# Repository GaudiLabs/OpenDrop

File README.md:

## OpenDrop 

Open Source Digital Microfluidics Bio Lab

### Don't click on the files!
Click on the "Download ZIP" Button to the right.
Then unpack the archive.

### Open Source Digital Microfluidics Bio Lab

OpenDrop is a new open source digital microfludics platform for research purposes. The device uses recent electro-wetting technology to control small droplets of liquids. Potential applications include lab-on-a-chip devices for automating processes of digital biology. However, the present design should also open up the technology to other fields, such as art, music, games, and education. It should also allow experimentation for the purpose of finding new applications. 

For more info on the open source project see:

http://www.gaudi.ch/OpenDrop

### License

OpenDrop, all design files and software are licensed under a GNU GENERAL PUBLIC LICENSE
See license file in the repository.

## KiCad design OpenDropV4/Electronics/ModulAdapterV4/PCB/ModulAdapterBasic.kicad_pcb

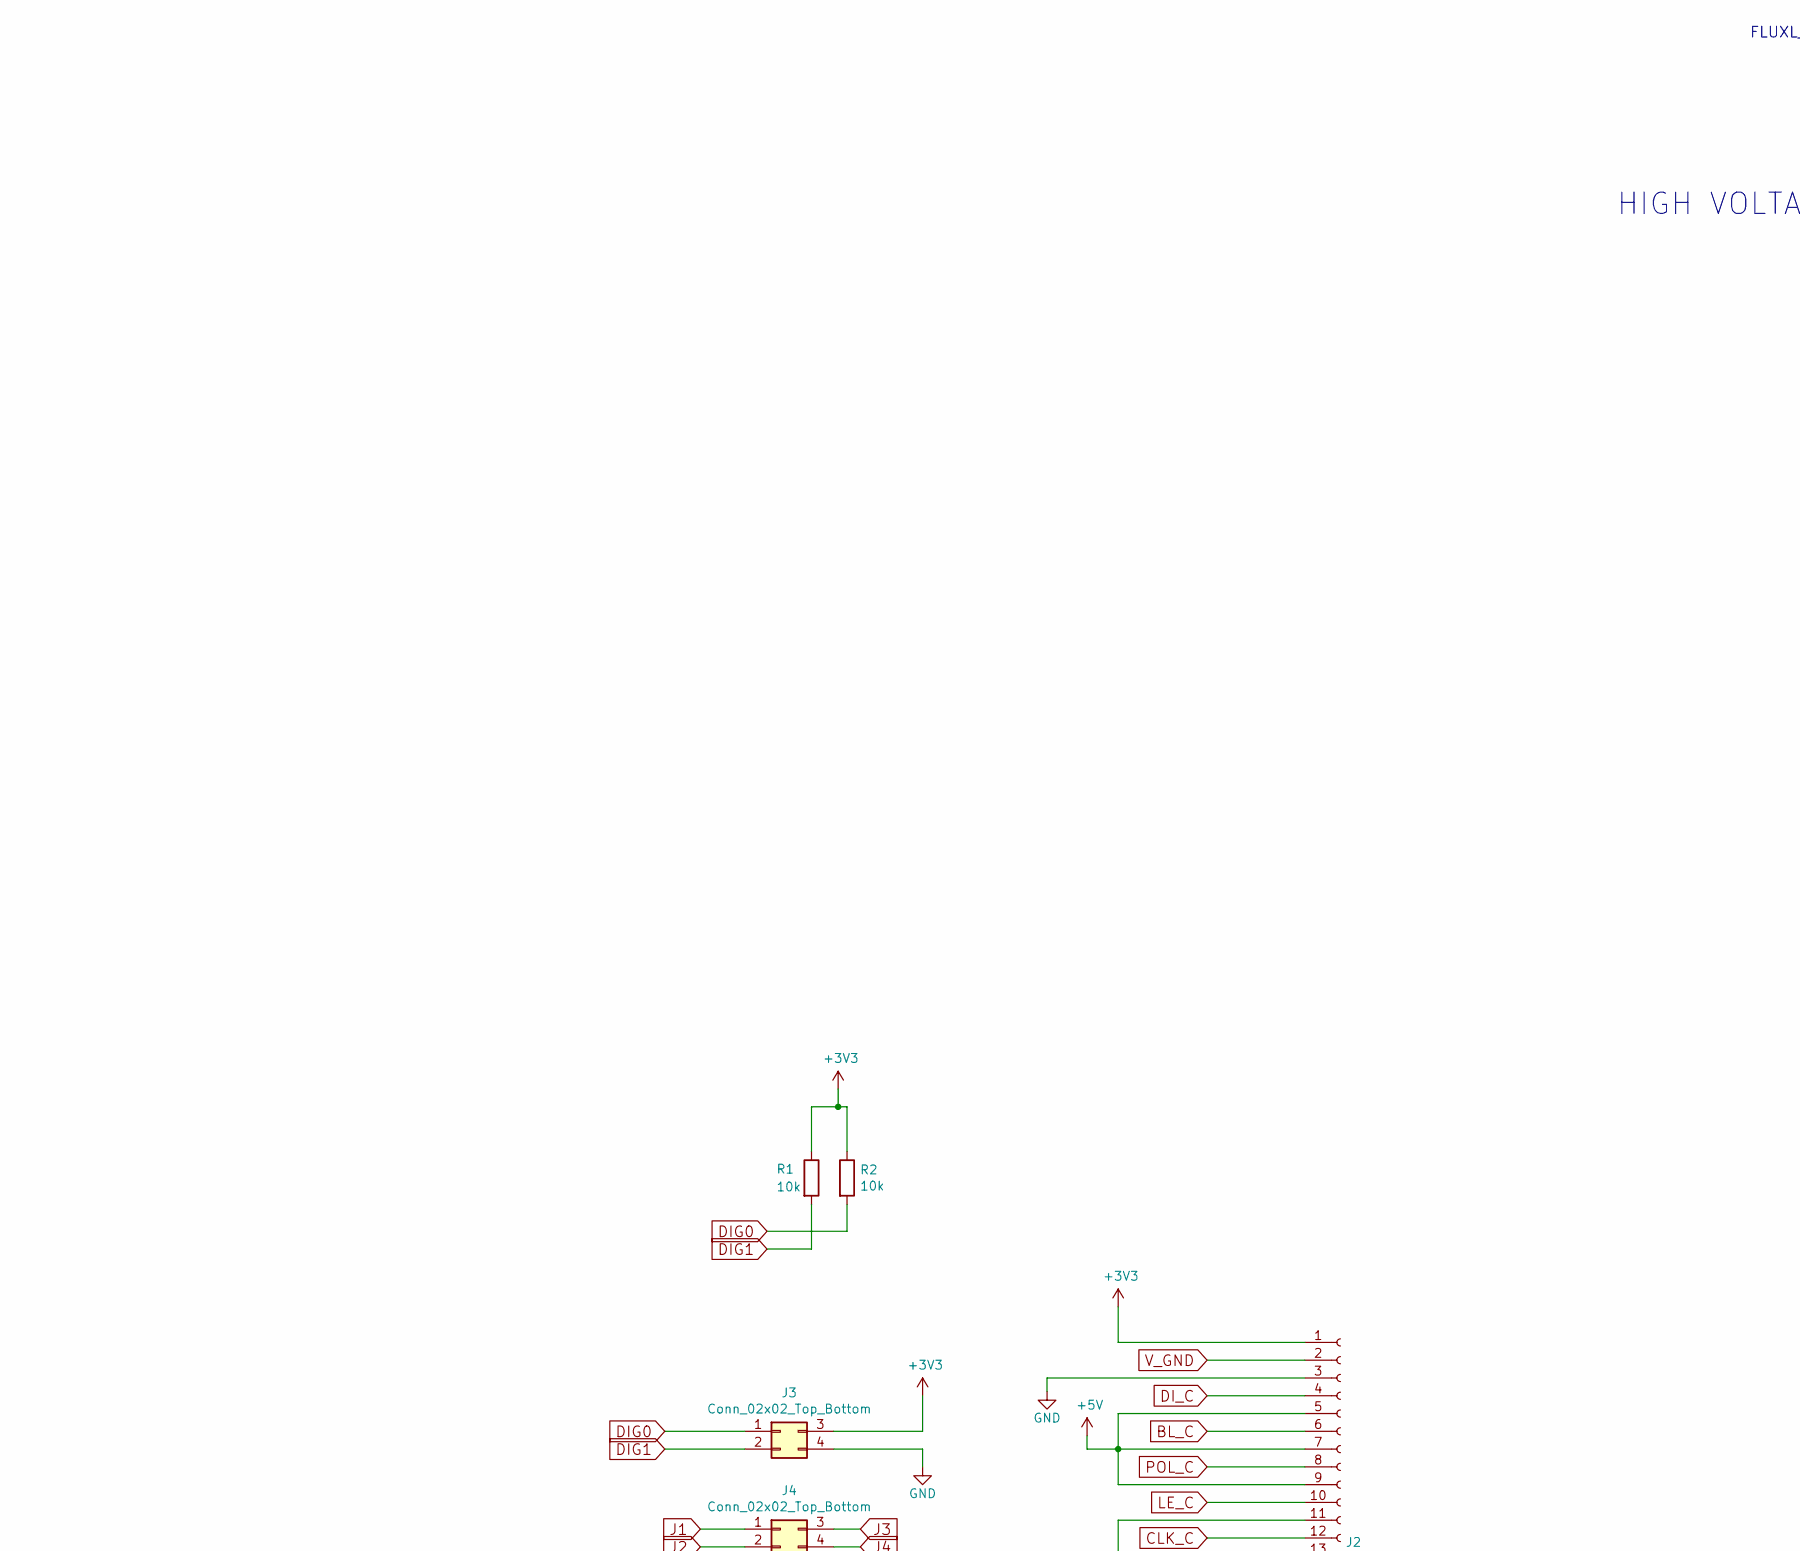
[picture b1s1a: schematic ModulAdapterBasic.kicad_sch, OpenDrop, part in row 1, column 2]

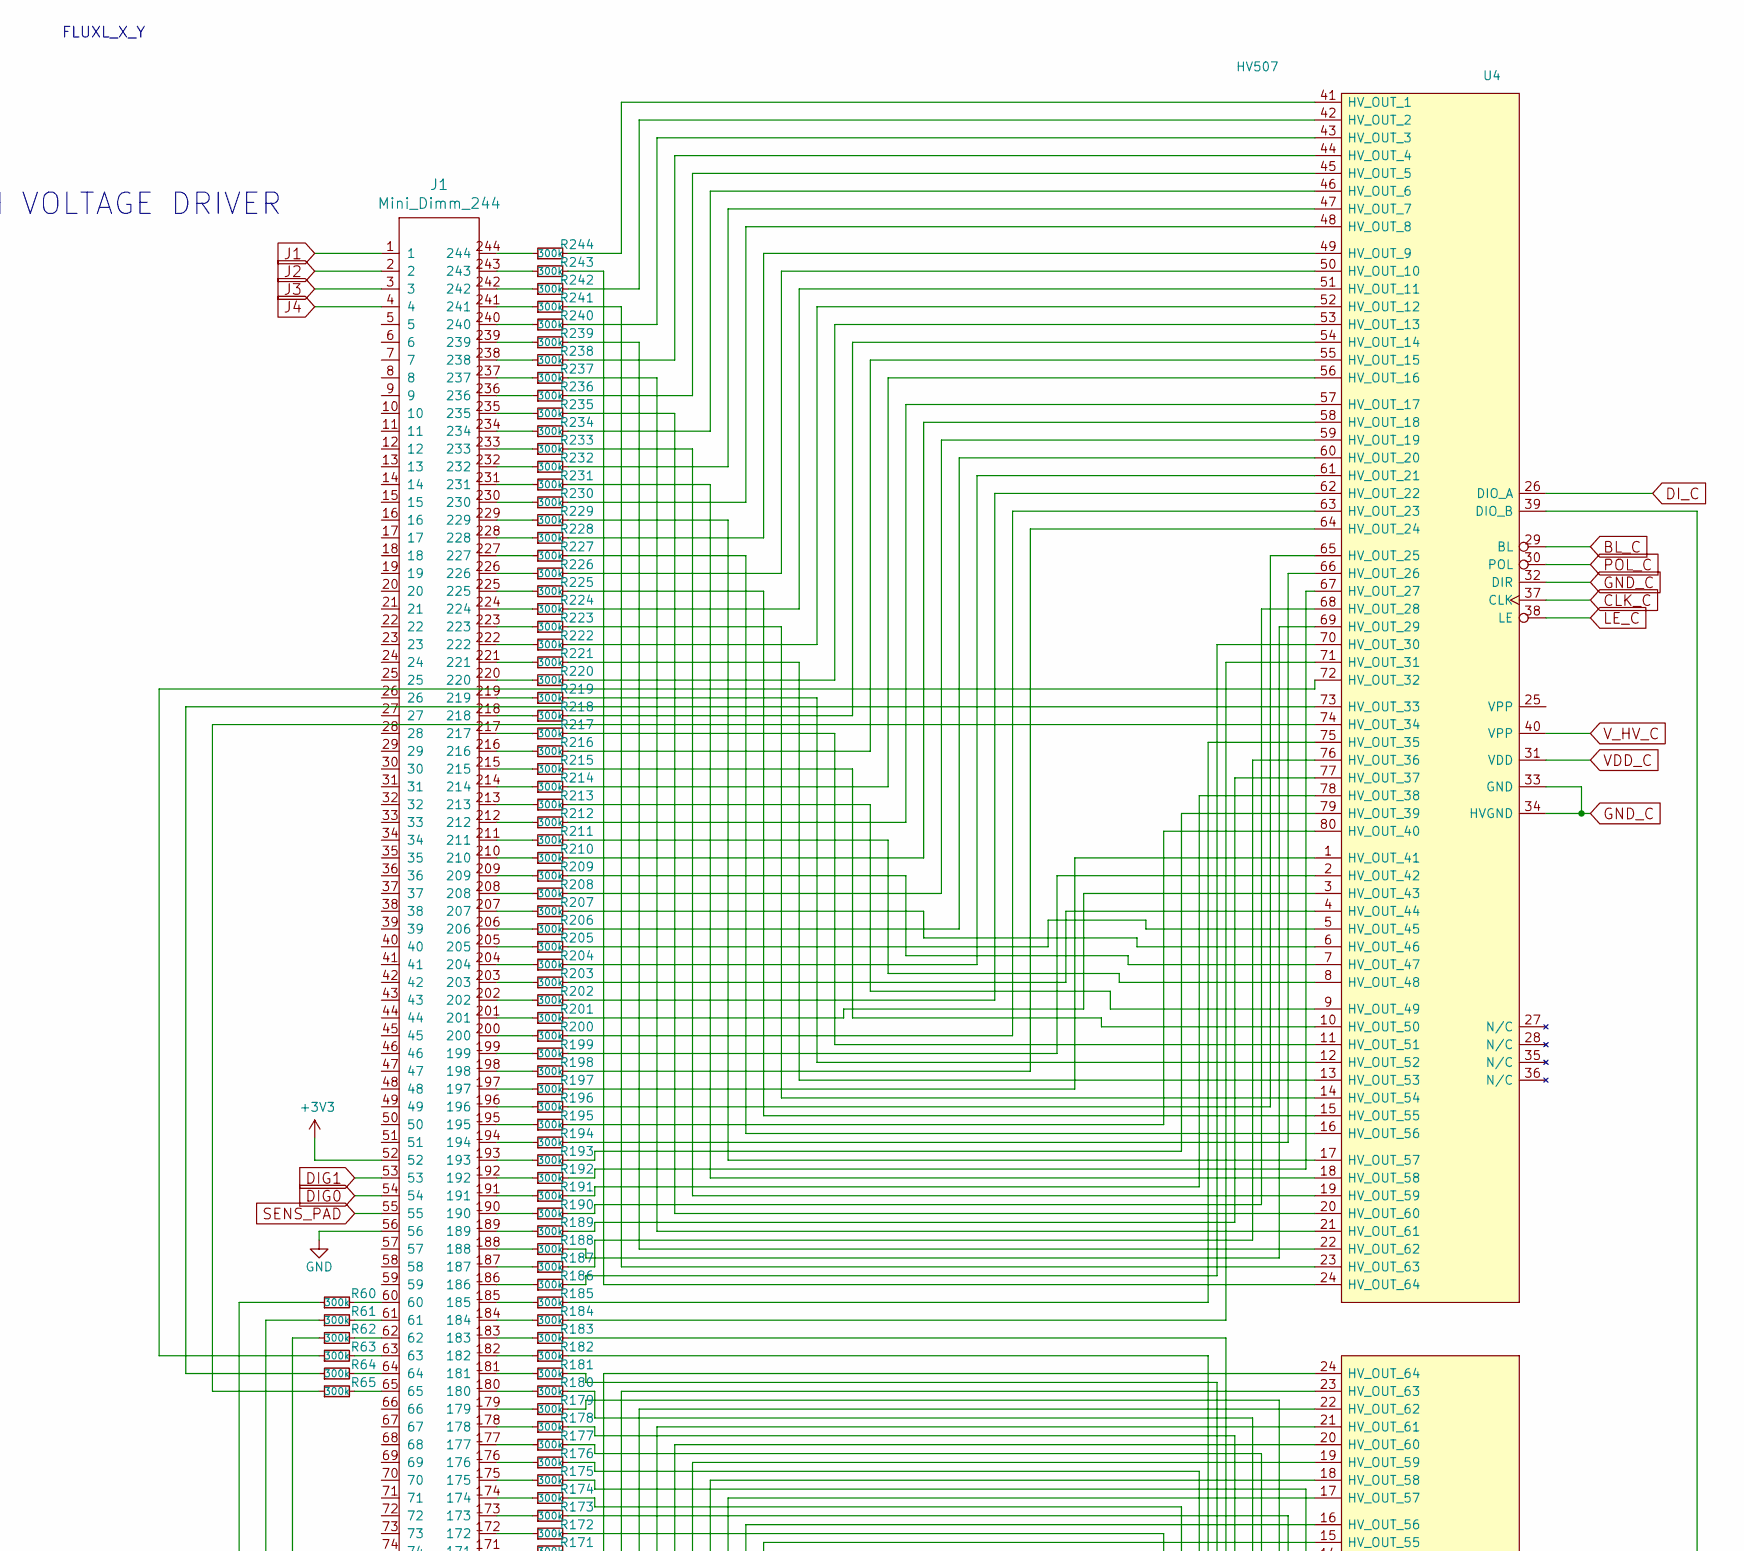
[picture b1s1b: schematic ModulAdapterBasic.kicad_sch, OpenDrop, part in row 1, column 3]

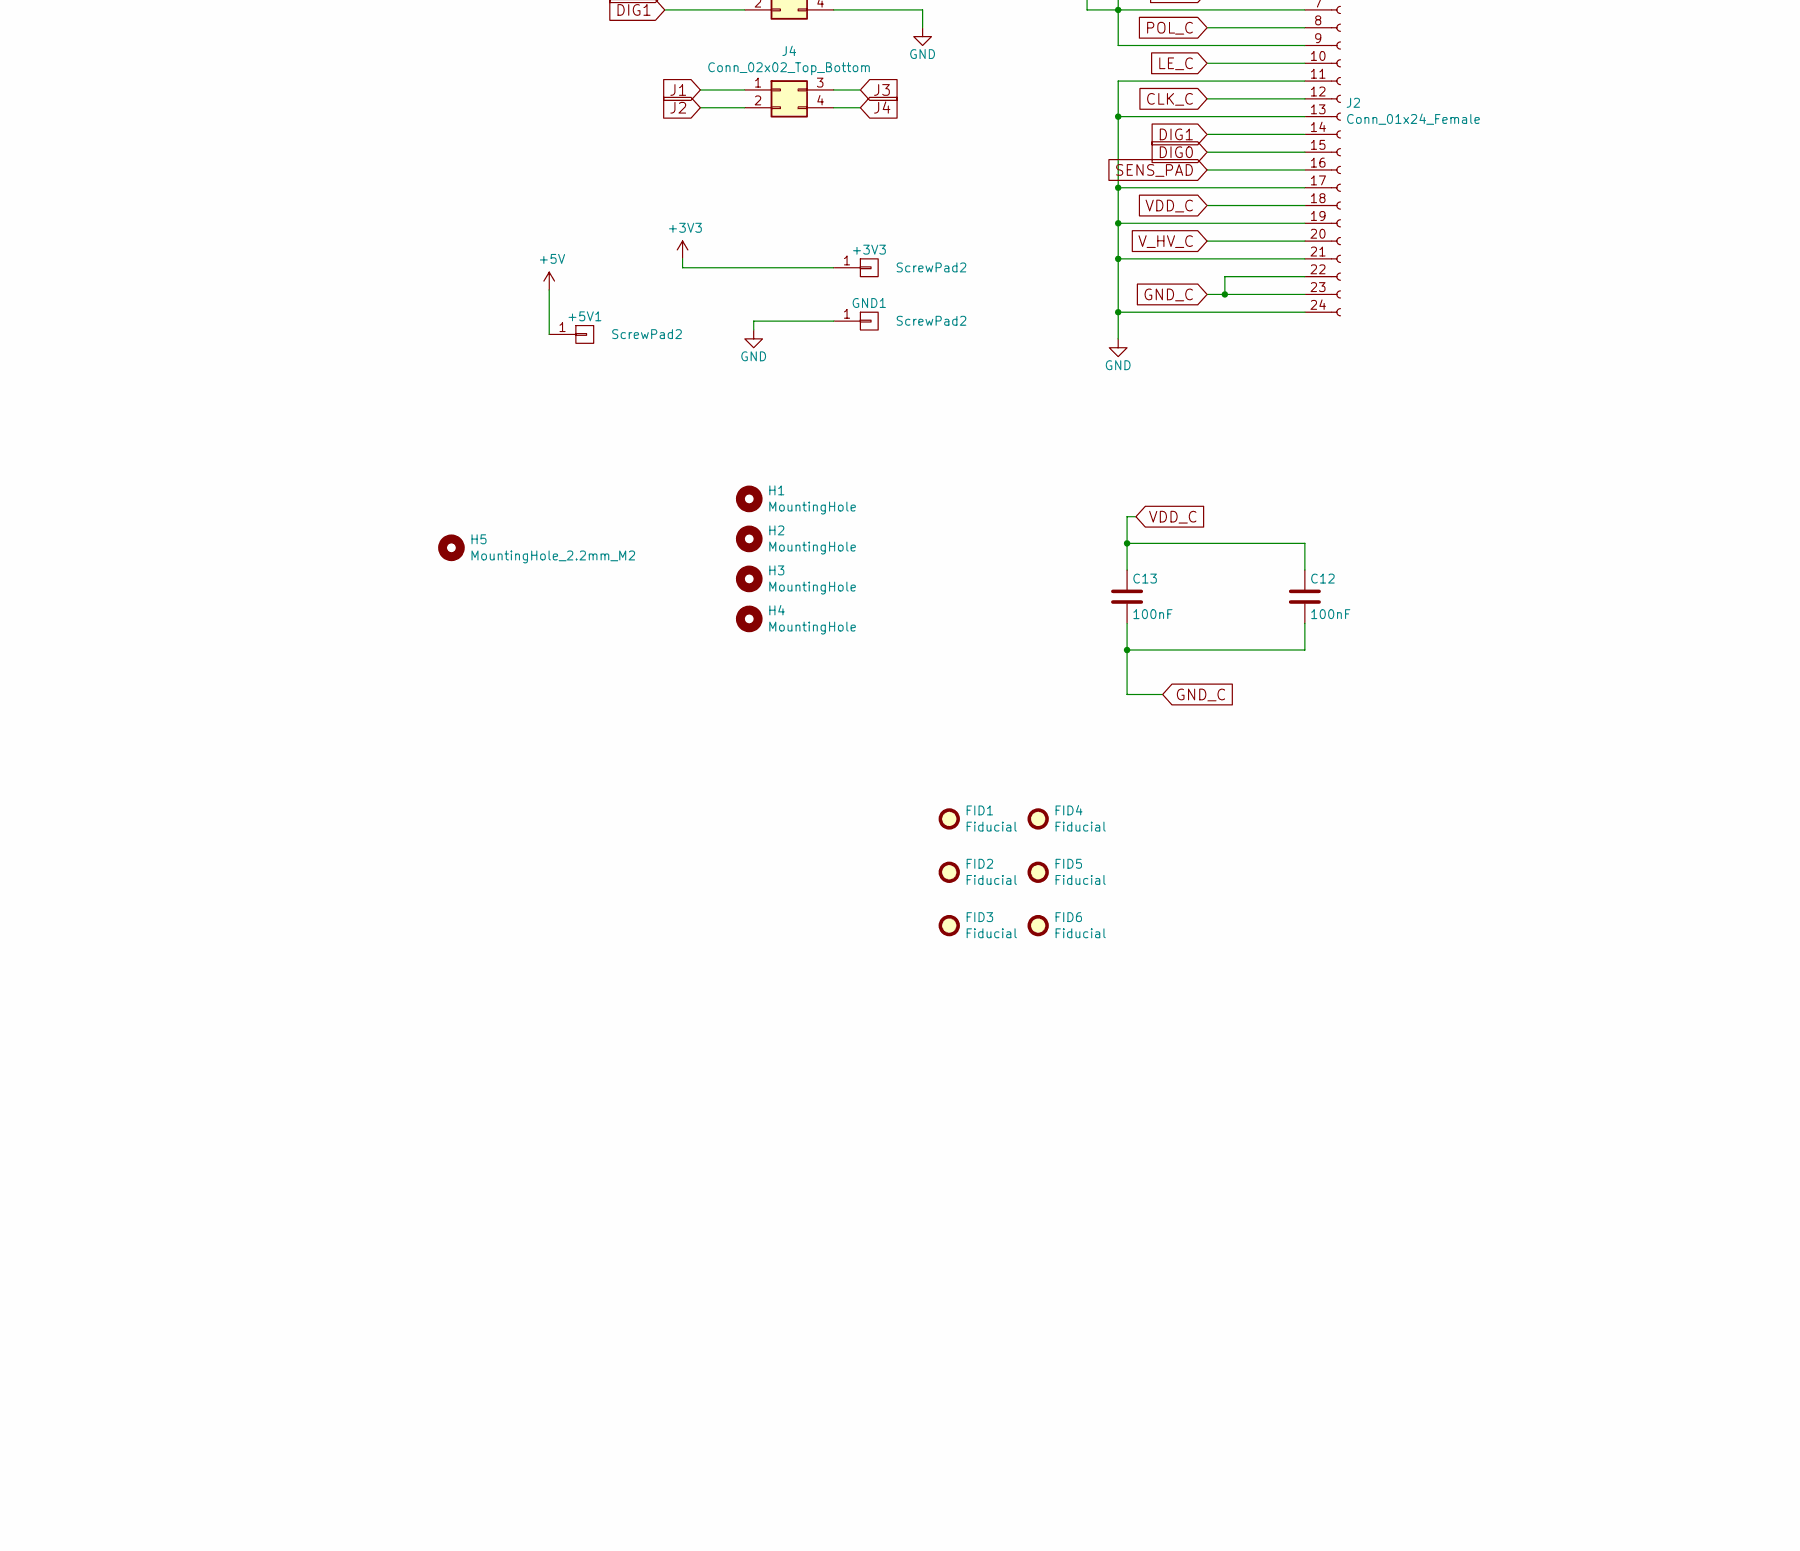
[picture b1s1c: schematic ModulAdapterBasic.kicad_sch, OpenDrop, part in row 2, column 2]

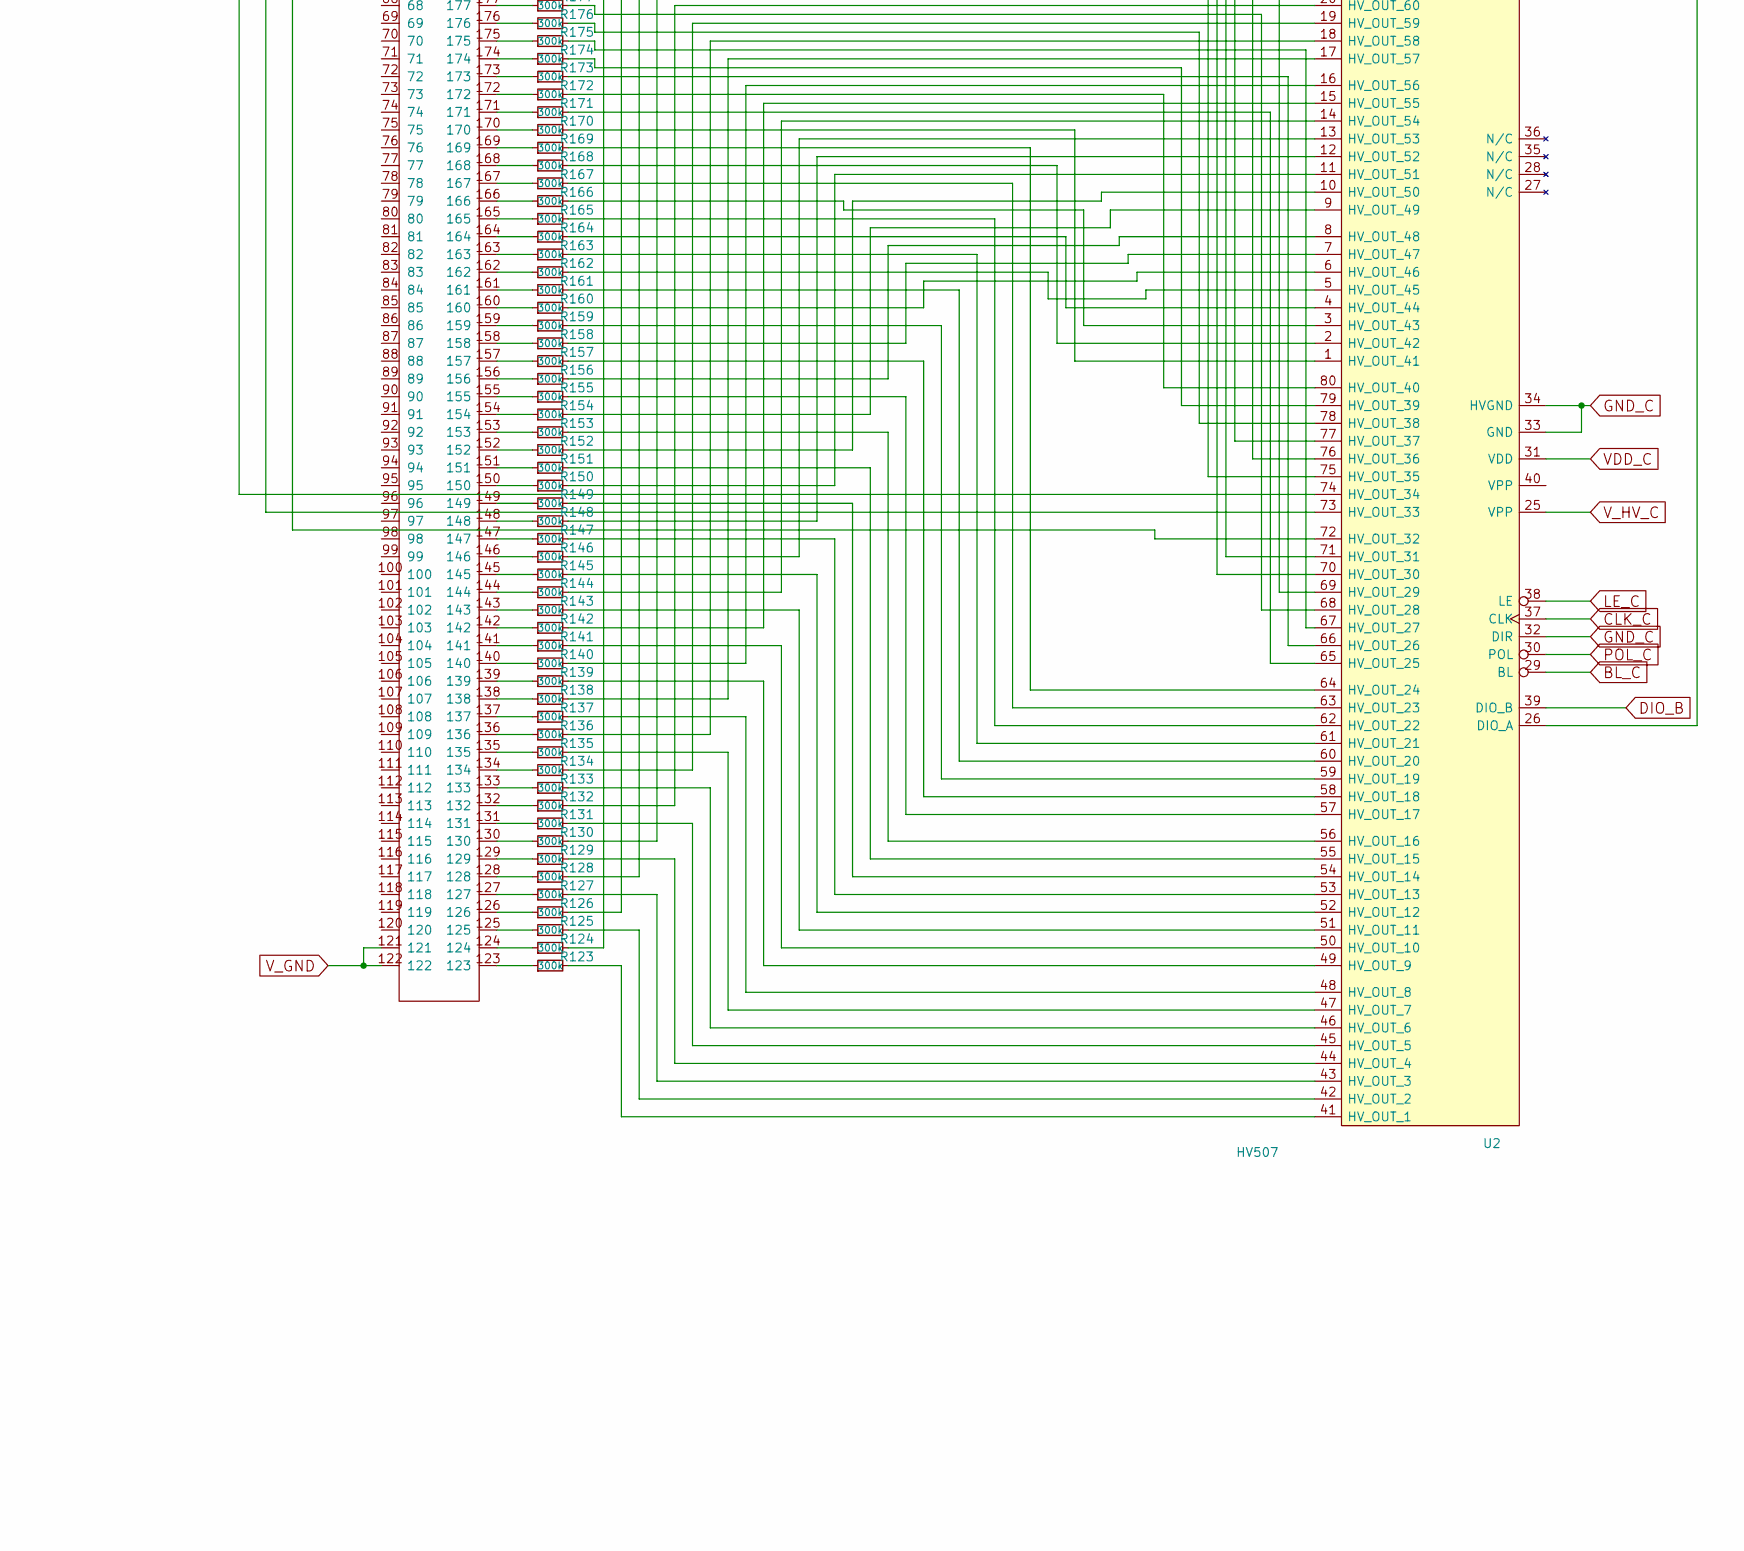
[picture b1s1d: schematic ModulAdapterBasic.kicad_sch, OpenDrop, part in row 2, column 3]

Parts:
+3V3, +5V1: ScrewPad2; Measurement_Point_Square-SMD-Pad_Small
C12, C13: 100nF; C_0603_1608Metric
FID1, FID2, FID3, FID4, FID5, FID6: Fiducial; Fiducial_1mm_Dia_2.54mm_Outer_CopperBottom
GND1: ScrewPad2; Measurement_Point_Square-SMD-Pad_Small
H1, H2, H3, H4: MountingHole; MountingHoleM3
H5: MountingHole_2.2mm_M2
J1: Mini_Dimm_244; MiniDimm_06_244_200
J2: Conn_01x24_Female; FFC_MOLEX_EASYON_05mm_24
J3, J4: Conn_02x02_Top_Bottom; PinHeader_2x02_P2.00mm_Vertical
R1, R2: 10k; R_0603_1608Metric
R60, R61, R62, R63, R64, R65, R123, R124, R125, R126, R127, R128, R129, R130, R131, R132, R133, R134, R135, R136, R137, R138, R139, R140, R141, R142, R143, R144, R145, R146, R147, R148, R149, R150, R151, R152, R153, R154, R155, R156, R157, R158, R159, R160, R161, R162, R163, R164, R165, R166, R167, R168, R169, R170, R171, R172, R173, R174, R175, R176, R177, R178, R179, R180, R181, R182, R183, R184, R185, R186, R187, R188, R189, R190, R191, R192, R193, R194, R195, R196, R197, R198, R199, R200, R201, R202, R203, R204, R205, R206, R207, R208, R209, R210, R211, R212, R213, R214, R215, R216, R217, R218, R219, R220, R221, R222, R223, R224, R225, R226, R227, R228, R229, R230, R231, R232, R233, R234, R235, R236, R237, R238, R239, R240, R241, R242, R243, R244: 300k; R_0402_1005Metric
U2, U4: HV507; PQFP-80_14x20mm_Pitch0.8mm

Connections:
+3V3: +3V3.1, J1.52, J2.1, J3.3, R1.1, R2.1
+5V: +5V1.1, J2.5, J2.7, J2.9
BL_C: J2.6, U2.29 (BL), U4.29 (BL)
CLK_C: J2.12, U2.37 (CLK), U4.37 (CLK)
DIG0: J1.54, J2.15, J3.1, R2.2
DIG1: J1.53, J2.14, J3.2, R1.2
DIO_B: U2.39 (DIO_B)
DI_C: J2.4, U4.26 (DIO_A)
GND: GND1.1, J1.56, J2.3, J2.11, J2.13, J2.17, J2.19, J2.21, J2.24, J3.4
GND_C: C12.2, C13.2, J2.22, J2.23, U2.32 (DIR), U2.33 (GND), U2.34 (HVGND), U4.32 (DIR), U4.33 (GND), U4.34 (HVGND)
J1: J1.1, J4.1
J2: J1.2, J4.2
J3: J1.3, J4.3
J4: J1.4, J4.4
LE_C: J2.10, U2.38 (LE), U4.38 (LE)
unnamed: J1.60, R60.2
unnamed: J1.61, R61.2
unnamed: J1.62, R62.2
unnamed: J1.63, R63.2
unnamed: J1.64, R64.2
unnamed: J1.65, R65.2
unnamed: J1.123, R123.1
unnamed: J1.124, R124.1
unnamed: J1.125, R125.1
unnamed: J1.126, R126.1
unnamed: J1.127, R127.1
unnamed: J1.128, R128.1
unnamed: J1.129, R129.1
unnamed: J1.130, R130.1
unnamed: J1.131, R131.1
unnamed: J1.132, R132.1
unnamed: J1.133, R133.1
unnamed: J1.134, R134.1
unnamed: J1.135, R135.1
unnamed: J1.136, R136.1
unnamed: J1.137, R137.1
unnamed: J1.138, R138.1
unnamed: J1.139, R139.1
unnamed: J1.140, R140.1
unnamed: J1.141, R141.1
unnamed: J1.142, R142.1
unnamed: J1.143, R143.1
unnamed: J1.144, R144.1
unnamed: J1.145, R145.1
unnamed: J1.146, R146.1
unnamed: J1.147, R147.1
unnamed: J1.148, R148.1
unnamed: J1.149, R149.1
unnamed: J1.150, R150.1
unnamed: J1.151, R151.1
unnamed: J1.152, R152.1
unnamed: J1.153, R153.1
unnamed: J1.154, R154.1
unnamed: J1.155, R155.1
unnamed: J1.156, R156.1
unnamed: J1.157, R157.1
unnamed: J1.158, R158.1
unnamed: J1.159, R159.1
unnamed: J1.160, R160.1
unnamed: J1.161, R161.1
unnamed: J1.162, R162.1
unnamed: J1.163, R163.1
unnamed: J1.164, R164.1
unnamed: J1.165, R165.1
unnamed: J1.166, R166.1
unnamed: J1.167, R167.1
unnamed: J1.168, R168.1
unnamed: J1.169, R169.1
unnamed: J1.170, R170.1
unnamed: J1.171, R171.1
unnamed: J1.172, R172.1
unnamed: J1.173, R173.1
unnamed: J1.174, R174.1
unnamed: J1.175, R175.1
unnamed: J1.176, R176.1
unnamed: J1.177, R177.1
unnamed: J1.178, R178.1
unnamed: J1.179, R179.1
unnamed: J1.180, R180.1
unnamed: J1.181, R181.1
unnamed: J1.182, R182.1
unnamed: J1.183, R183.1
unnamed: J1.184, R184.1
unnamed: J1.185, R185.1
unnamed: J1.186, R186.1
unnamed: J1.187, R187.1
unnamed: J1.188, R188.1
unnamed: J1.189, R189.1
unnamed: J1.190, R190.1
unnamed: J1.191, R191.1
unnamed: J1.192, R192.1
unnamed: J1.193, R193.1
unnamed: J1.194, R194.1
unnamed: J1.195, R195.1
unnamed: J1.196, R196.1
unnamed: J1.197, R197.1
unnamed: J1.198, R198.1
unnamed: J1.199, R199.1
unnamed: J1.200, R200.1
unnamed: J1.201, R201.1
unnamed: J1.202, R202.1
unnamed: J1.203, R203.1
unnamed: J1.204, R204.1
unnamed: J1.205, R205.1
unnamed: J1.206, R206.1
unnamed: J1.207, R207.1
unnamed: J1.208, R208.1
unnamed: J1.209, R209.1
unnamed: J1.210, R210.1
unnamed: J1.211, R211.1
unnamed: J1.212, R212.1
unnamed: J1.213, R213.1
unnamed: J1.214, R214.1
unnamed: J1.215, R215.1
unnamed: J1.216, R216.1
unnamed: J1.217, R217.1
unnamed: J1.218, R218.1
unnamed: J1.219, R219.1
unnamed: J1.220, R220.1
unnamed: J1.221, R221.1
unnamed: J1.222, R222.1
unnamed: J1.223, R223.1
unnamed: J1.224, R224.1
unnamed: J1.225, R225.1
unnamed: J1.226, R226.1
unnamed: J1.227, R227.1
unnamed: J1.228, R228.1
unnamed: J1.229, R229.1
unnamed: J1.230, R230.1
unnamed: J1.231, R231.1
unnamed: J1.232, R232.1
unnamed: J1.233, R233.1
unnamed: J1.234, R234.1
unnamed: J1.235, R235.1
unnamed: J1.236, R236.1
unnamed: J1.237, R237.1
unnamed: J1.238, R238.1
unnamed: J1.239, R239.1
unnamed: J1.240, R240.1
unnamed: J1.241, R241.1
unnamed: J1.242, R242.1
unnamed: J1.243, R243.1
unnamed: J1.244, R244.1
unnamed: R60.1, U2.74 (HV_OUT_34)
unnamed: R61.1, U2.73 (HV_OUT_33)
unnamed: R62.1, U2.72 (HV_OUT_32)
unnamed: R63.1, U4.72 (HV_OUT_32)
unnamed: R64.1, U4.73 (HV_OUT_33)
unnamed: R65.1, U4.74 (HV_OUT_34)
unnamed: R123.2, U2.41 (HV_OUT_1)
unnamed: R124.2, U2.24 (HV_OUT_64)
unnamed: R125.2, U2.42 (HV_OUT_2)
unnamed: R126.2, U2.23 (HV_OUT_63)
unnamed: R127.2, U2.43 (HV_OUT_3)
unnamed: R128.2, U2.22 (HV_OUT_62)
unnamed: R129.2, U2.44 (HV_OUT_4)
unnamed: R130.2, U2.21 (HV_OUT_61)
unnamed: R131.2, U2.45 (HV_OUT_5)
unnamed: R132.2, U2.20 (HV_OUT_60)
unnamed: R133.2, U2.46 (HV_OUT_6)
unnamed: R134.2, U2.19 (HV_OUT_59)
unnamed: R135.2, U2.47 (HV_OUT_7)
unnamed: R136.2, U2.18 (HV_OUT_58)
unnamed: R137.2, U2.48 (HV_OUT_8)
unnamed: R138.2, U2.17 (HV_OUT_57)
unnamed: R139.2, U2.49 (HV_OUT_9)
unnamed: R140.2, U2.16 (HV_OUT_56)
unnamed: R141.2, U2.50 (HV_OUT_10)
unnamed: R142.2, U2.15 (HV_OUT_55)
unnamed: R143.2, U2.51 (HV_OUT_11)
unnamed: R144.2, U2.14 (HV_OUT_54)
unnamed: R145.2, U2.52 (HV_OUT_12)
unnamed: R146.2, U2.13 (HV_OUT_53)
unnamed: R147.2, U2.53 (HV_OUT_13)
unnamed: R148.2, U2.12 (HV_OUT_52)
unnamed: R149.2, U2.54 (HV_OUT_14)
unnamed: R150.2, U2.11 (HV_OUT_51)
unnamed: R151.2, U2.55 (HV_OUT_15)
unnamed: R152.2, U2.10 (HV_OUT_50)
unnamed: R153.2, U2.56 (HV_OUT_16)
unnamed: R154.2, U2.9 (HV_OUT_49)
unnamed: R155.2, U2.57 (HV_OUT_17)
unnamed: R156.2, U2.8 (HV_OUT_48)
unnamed: R157.2, U2.58 (HV_OUT_18)
unnamed: R158.2, U2.7 (HV_OUT_47)
unnamed: R159.2, U2.59 (HV_OUT_19)
unnamed: R160.2, U2.6 (HV_OUT_46)
unnamed: R161.2, U2.60 (HV_OUT_20)
unnamed: R162.2, U2.5 (HV_OUT_45)
unnamed: R163.2, U2.61 (HV_OUT_21)
unnamed: R164.2, U2.4 (HV_OUT_44)
unnamed: R165.2, U2.62 (HV_OUT_22)
unnamed: R166.2, U2.3 (HV_OUT_43)
unnamed: R167.2, U2.63 (HV_OUT_23)
unnamed: R168.2, U2.2 (HV_OUT_42)
unnamed: R169.2, U2.64 (HV_OUT_24)
unnamed: R170.2, U2.1 (HV_OUT_41)
unnamed: R171.2, U2.65 (HV_OUT_25)
unnamed: R172.2, U2.80 (HV_OUT_40)
unnamed: R173.2, U2.66 (HV_OUT_26)
unnamed: R174.2, U2.79 (HV_OUT_39)
unnamed: R175.2, U2.67 (HV_OUT_27)
unnamed: R176.2, U2.78 (HV_OUT_38)
unnamed: R177.2, U2.68 (HV_OUT_28)
unnamed: R178.2, U2.77 (HV_OUT_37)
unnamed: R179.2, U2.69 (HV_OUT_29)
unnamed: R180.2, U2.76 (HV_OUT_36)
unnamed: R181.2, U2.70 (HV_OUT_30)
unnamed: R182.2, U2.75 (HV_OUT_35)
unnamed: R183.2, U2.71 (HV_OUT_31)
unnamed: R184.2, U4.71 (HV_OUT_31)
unnamed: R185.2, U4.75 (HV_OUT_35)
unnamed: R186.2, U4.70 (HV_OUT_30)
unnamed: R187.2, U4.76 (HV_OUT_36)
unnamed: R188.2, U4.69 (HV_OUT_29)
unnamed: R189.2, U4.77 (HV_OUT_37)
unnamed: R190.2, U4.68 (HV_OUT_28)
unnamed: R191.2, U4.78 (HV_OUT_38)
unnamed: R192.2, U4.67 (HV_OUT_27)
unnamed: R193.2, U4.79 (HV_OUT_39)
unnamed: R194.2, U4.66 (HV_OUT_26)
unnamed: R195.2, U4.80 (HV_OUT_40)
unnamed: R196.2, U4.65 (HV_OUT_25)
unnamed: R197.2, U4.1 (HV_OUT_41)
unnamed: R198.2, U4.64 (HV_OUT_24)
unnamed: R199.2, U4.2 (HV_OUT_42)
unnamed: R200.2, U4.63 (HV_OUT_23)
unnamed: R201.2, U4.3 (HV_OUT_43)
unnamed: R202.2, U4.62 (HV_OUT_22)
unnamed: R203.2, U4.4 (HV_OUT_44)
unnamed: R204.2, U4.61 (HV_OUT_21)
unnamed: R205.2, U4.5 (HV_OUT_45)
unnamed: R206.2, U4.60 (HV_OUT_20)
unnamed: R207.2, U4.6 (HV_OUT_46)
unnamed: R208.2, U4.59 (HV_OUT_19)
unnamed: R209.2, U4.7 (HV_OUT_47)
unnamed: R210.2, U4.58 (HV_OUT_18)
unnamed: R211.2, U4.8 (HV_OUT_48)
unnamed: R212.2, U4.57 (HV_OUT_17)
unnamed: R213.2, U4.9 (HV_OUT_49)
unnamed: R214.2, U4.56 (HV_OUT_16)
unnamed: R215.2, U4.10 (HV_OUT_50)
unnamed: R216.2, U4.55 (HV_OUT_15)
unnamed: R217.2, U4.11 (HV_OUT_51)
unnamed: R218.2, U4.54 (HV_OUT_14)
unnamed: R219.2, U4.12 (HV_OUT_52)
unnamed: R220.2, U4.53 (HV_OUT_13)
unnamed: R221.2, U4.13 (HV_OUT_53)
unnamed: R222.2, U4.52 (HV_OUT_12)
unnamed: R223.2, U4.14 (HV_OUT_54)
unnamed: R224.2, U4.51 (HV_OUT_11)
unnamed: R225.2, U4.15 (HV_OUT_55)
unnamed: R226.2, U4.50 (HV_OUT_10)
unnamed: R227.2, U4.16 (HV_OUT_56)
unnamed: R228.2, U4.49 (HV_OUT_9)
unnamed: R229.2, U4.17 (HV_OUT_57)
unnamed: R230.2, U4.48 (HV_OUT_8)
unnamed: R231.2, U4.18 (HV_OUT_58)
unnamed: R232.2, U4.47 (HV_OUT_7)
unnamed: R233.2, U4.19 (HV_OUT_59)
unnamed: R234.2, U4.46 (HV_OUT_6)
unnamed: R235.2, U4.20 (HV_OUT_60)
unnamed: R236.2, U4.45 (HV_OUT_5)
unnamed: R237.2, U4.21 (HV_OUT_61)
unnamed: R238.2, U4.44 (HV_OUT_4)
unnamed: R239.2, U4.22 (HV_OUT_62)
unnamed: R240.2, U4.43 (HV_OUT_3)
unnamed: R241.2, U4.23 (HV_OUT_63)
unnamed: R242.2, U4.42 (HV_OUT_2)
unnamed: R243.2, U4.24 (HV_OUT_64)
unnamed: R244.2, U4.41 (HV_OUT_1)
unnamed: U2.26 (DIO_A), U4.39 (DIO_B)
POL_C: J2.8, U2.30 (POL), U4.30 (POL)
SENS_PAD: J1.55, J2.16
VDD_C: C12.1, C13.1, J2.18, U2.31 (VDD), U4.31 (VDD)
V_GND: J1.121, J1.122, J2.2
V_HV_C: J2.20, U2.25 (VPP), U4.40 (VPP)

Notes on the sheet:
FLUXL_X_Y
HIGH VOLTAGE DRIVER

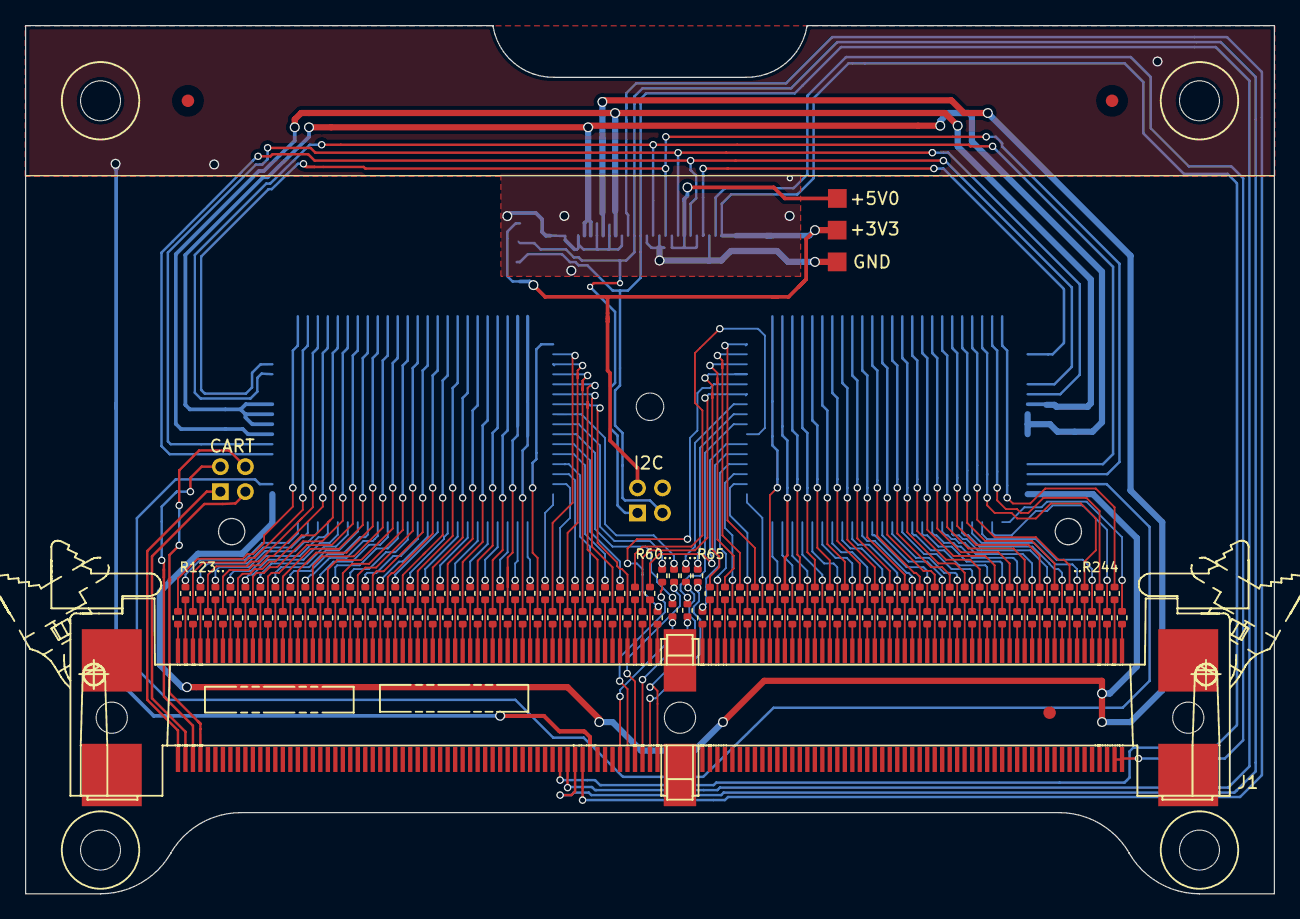
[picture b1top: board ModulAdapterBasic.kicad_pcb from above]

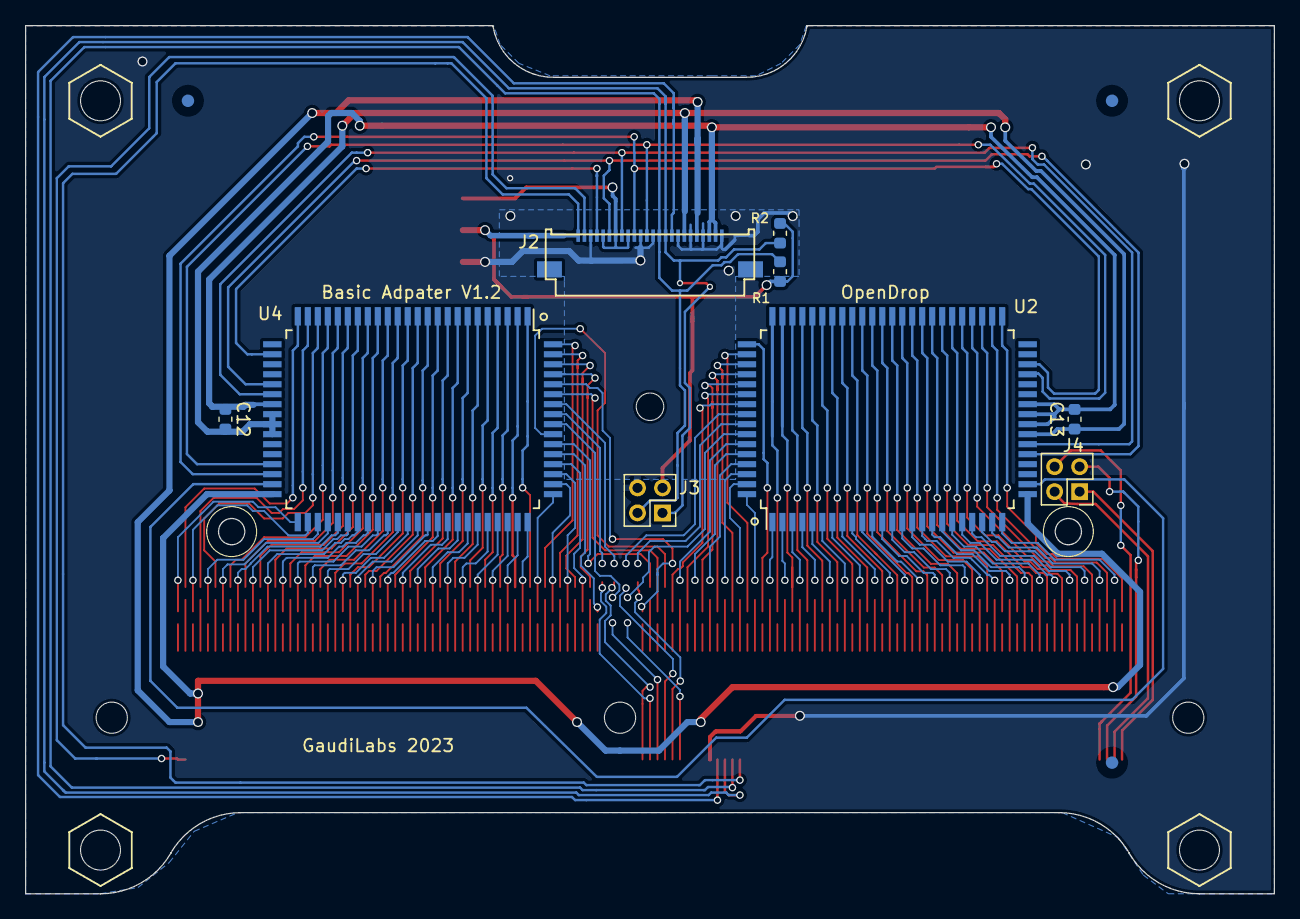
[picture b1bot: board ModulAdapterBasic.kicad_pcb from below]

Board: 2 copper layers, 100.0 x 69.5 mm, 152 parts (12 on the bottom side), 276 nets.
